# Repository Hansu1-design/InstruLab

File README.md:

# InstruLab — FPGA-TDC精密时间间隔测量仪器

## 项目概述
基于FPGA的精密时间间隔测量仪器，融合公开文献调研TDC方向核心成果：
- 赵雪鹏(硕士): 高分辨率TDC(5ps/60ps)
- 梁东飞: 触发抖动消除(19.3ps系统抖动)
- 脉冲延迟电路(10ps精度/10⁵s量程)

## 硬件架构
```
外触发 → 抖动消除 → 粗计数(49bit@400MHz) → 数据融合 → USB/SPI → PC
                  → TAC细测量(1.5ps) → 16bit ADC →┘
```

## 目录结构
```

├── rtl/               # FPGA源码(Verilog/VHDL,含testbench)
│   ├── tdc_modules.v / tdc_extra.v      # 粗计数+TAC+抖动消除+数据融合+SPI
│   ├── carry4_tdc.v / adc_ad7980.v / clk_gen.v   # TDC进位链/ADC/时钟
│   └── *_tb.v                          # 各模块仿真testbench
├── software/          # PC上位机
│   ├── tdc_controller.py    # CLI+GUI控制程序
│   └── tdc_calibration.py   # 校准程序
├── pcb/               # KiCad自动化脚本与TDC子板工程(dsn/BOM/操作手册)
├── data/              # 校准LUT与测量数据
├── docs/              # 设计规则/电源树/PCB规范
└── README.md          # 本文件
```

## 一键运行
```bash
cd software
python tdc_controller.py
```

## 验证状态
- FPGA顶层设计: ✅ iverilog编译通过
- 粗计数器49bit: ✅ 量程391h
- 抖动消除: ✅ C验证RSS 0.3%偏差
- TAC分辨率: ✅ 0.76ps(理论)/1.5ps(电路级)
- 数据融合: ✅ SPI 65bit输出
- 上位机: ✅ CLI模式通过

## 论文支撑
1. 赵雪鹏. 高分辨率时间间隔测量技术研究与实现[D]. 中北大学, 2022.
2. 梁东飞, 苏淑靖等. 一种用于脉冲延时发生器中消除触发抖动的方法[J]. 电子器件.
3. 苏淑靖组. 一种高精度脉冲延迟电路设计[J]. 中国测试, 2025.

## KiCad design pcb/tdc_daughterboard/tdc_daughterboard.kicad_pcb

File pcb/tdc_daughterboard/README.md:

# TDC Daughterboard 使用说明

## 打开项目
1. 双击桌面 KiCad 10.0 图标
2. 文件 → 打开 → 选择 tdc_daughterboard.kicad_pro

## 查看/修改原理图
3. 点击"原理图编辑器" → 查看完整电路
4. 如需添加器件: 放置 → 符号 → 从库选择

## PCB布局布线
5. 点击"PCB编辑器" → 查看当前布局
6. 布线规则: 模拟信号0.3mm, 电源0.5mm, GND尽量宽
7. 关键注意事项:
   - C1(100pF)紧贴AD7980 IN+引脚
   - 模拟GND和数字GND在AD7980下方单点连接
   - REF5050远离开关电源区域

## 生成Gerber(发板打样)
8. 文件 → 制造输出 → Gerber文件
9. 选择所有层, 输出到 gerber/ 目录
10. 文件 → 制造输出 → 钻孔文件
11. 打包所有文件 → 发给PCB厂商

## 板卡参数
- 尺寸: 50 x 40 mm
- 层数: 4 (Top/GND/PWR/Bottom)
- 厚度: 1.6mm
- 铜厚: 1oz
- 最小线宽/间距: 0.2mm/0.2mm
- BOM成本: ~$20 (不含PCB打样费)

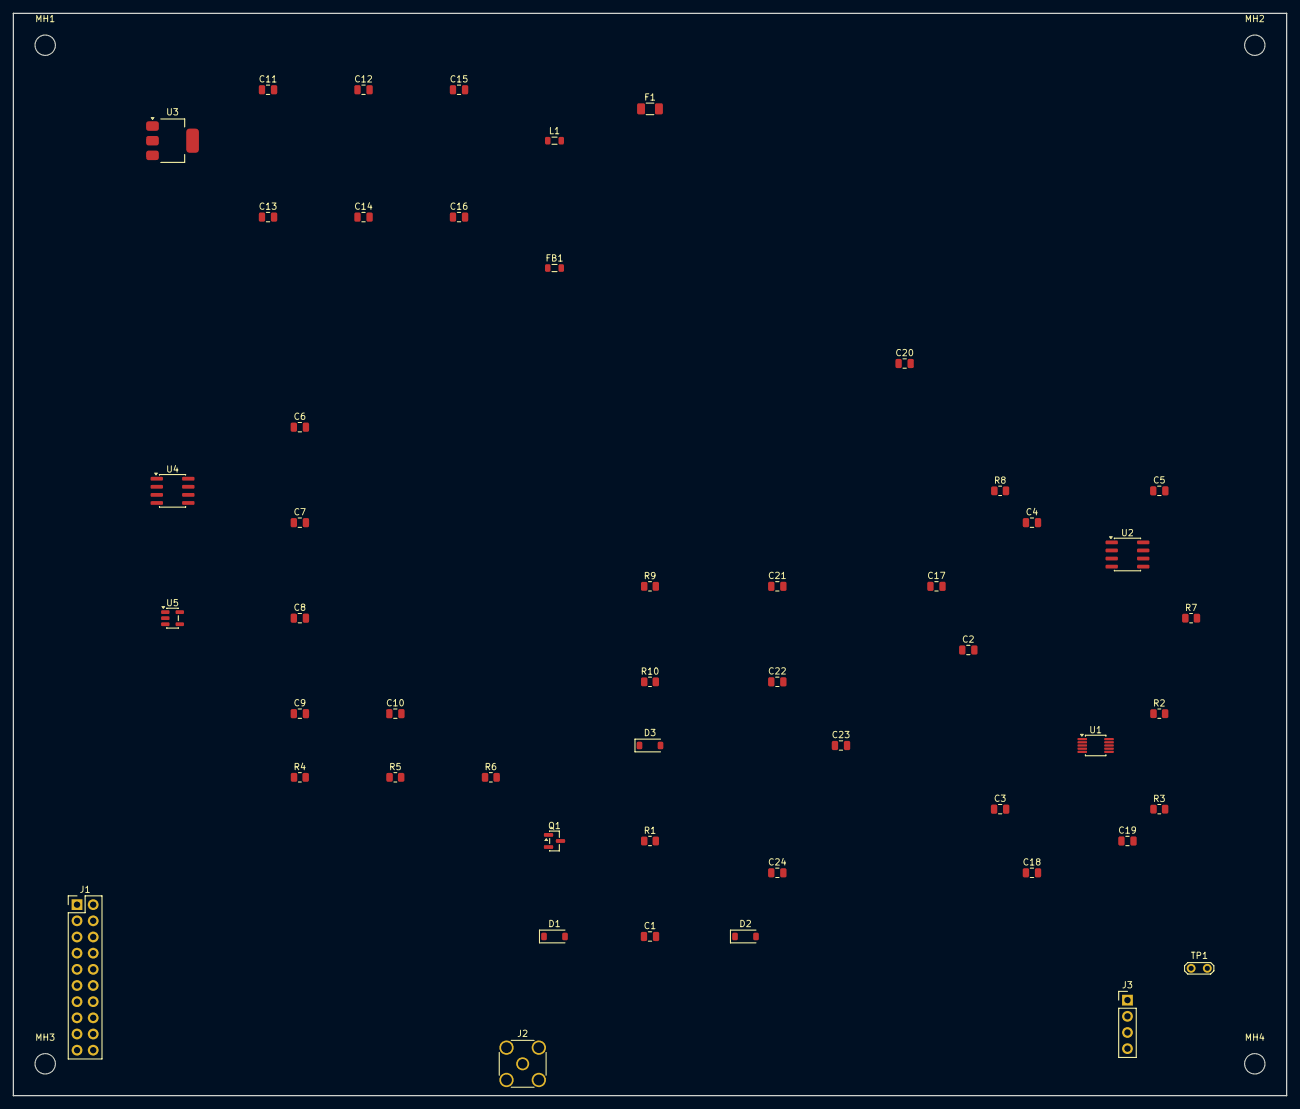
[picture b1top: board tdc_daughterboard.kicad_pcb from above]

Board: 4 copper layers, 200.0 x 170.0 mm, 54 parts (0 on the bottom side), 13 nets, no tracks yet.

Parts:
C1, C2, C3, C4, C5, C6, C7, C8, C9, C10, C11, C12, C13, C14, C15, C16, C17, C18, C19, C20, C21, C22, C23, C24: C_0805_2012Metric
D1, D2, D3: D_SOD-123
F1: Fuse_1206_3216Metric
FB1: L_0805_2012Metric
J1: PinHeader_2x10_P2.54mm_Vertical
J2: SMA_Amphenol_132134_Vertical
J3: PinHeader_1x04_P2.54mm_Vertical
L1: L_0805_2012Metric
MH1, MH2, MH3, MH4: MountingHole_3.2mm_M3
Q1: SOT-23
R1, R2, R3, R4, R5, R6, R7, R8, R9, R10: R_0805_2012Metric
TP1: TestPoint_2Pads_Pitch2.54mm_Drill0.8mm
U1: MSOP-10_3x3mm_P0.5mm
U2, U4: SOIC-8_3.9x4.9mm_P1.27mm
U3: SOT-223-3_TabPin2
U5: SOT-23-5

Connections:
ADC_IN: C1.2, U1.10
CS: J1.1, U1.5
EN: J1.7, U3.1
GND: D2.1, J2.2
MISO: J1.4, U1.4
MOSI: J1.3, U1.2
RST: J1.8, U1.1
SCLK: J1.2, U1.3
SIG: J2.1, R1.1
TAC: C1.1, R1.2
V5V: J1.6, U2.1
VDD: J1.5, U1.6, U3.2, U3.3
VREF: U1.7, U2.2
